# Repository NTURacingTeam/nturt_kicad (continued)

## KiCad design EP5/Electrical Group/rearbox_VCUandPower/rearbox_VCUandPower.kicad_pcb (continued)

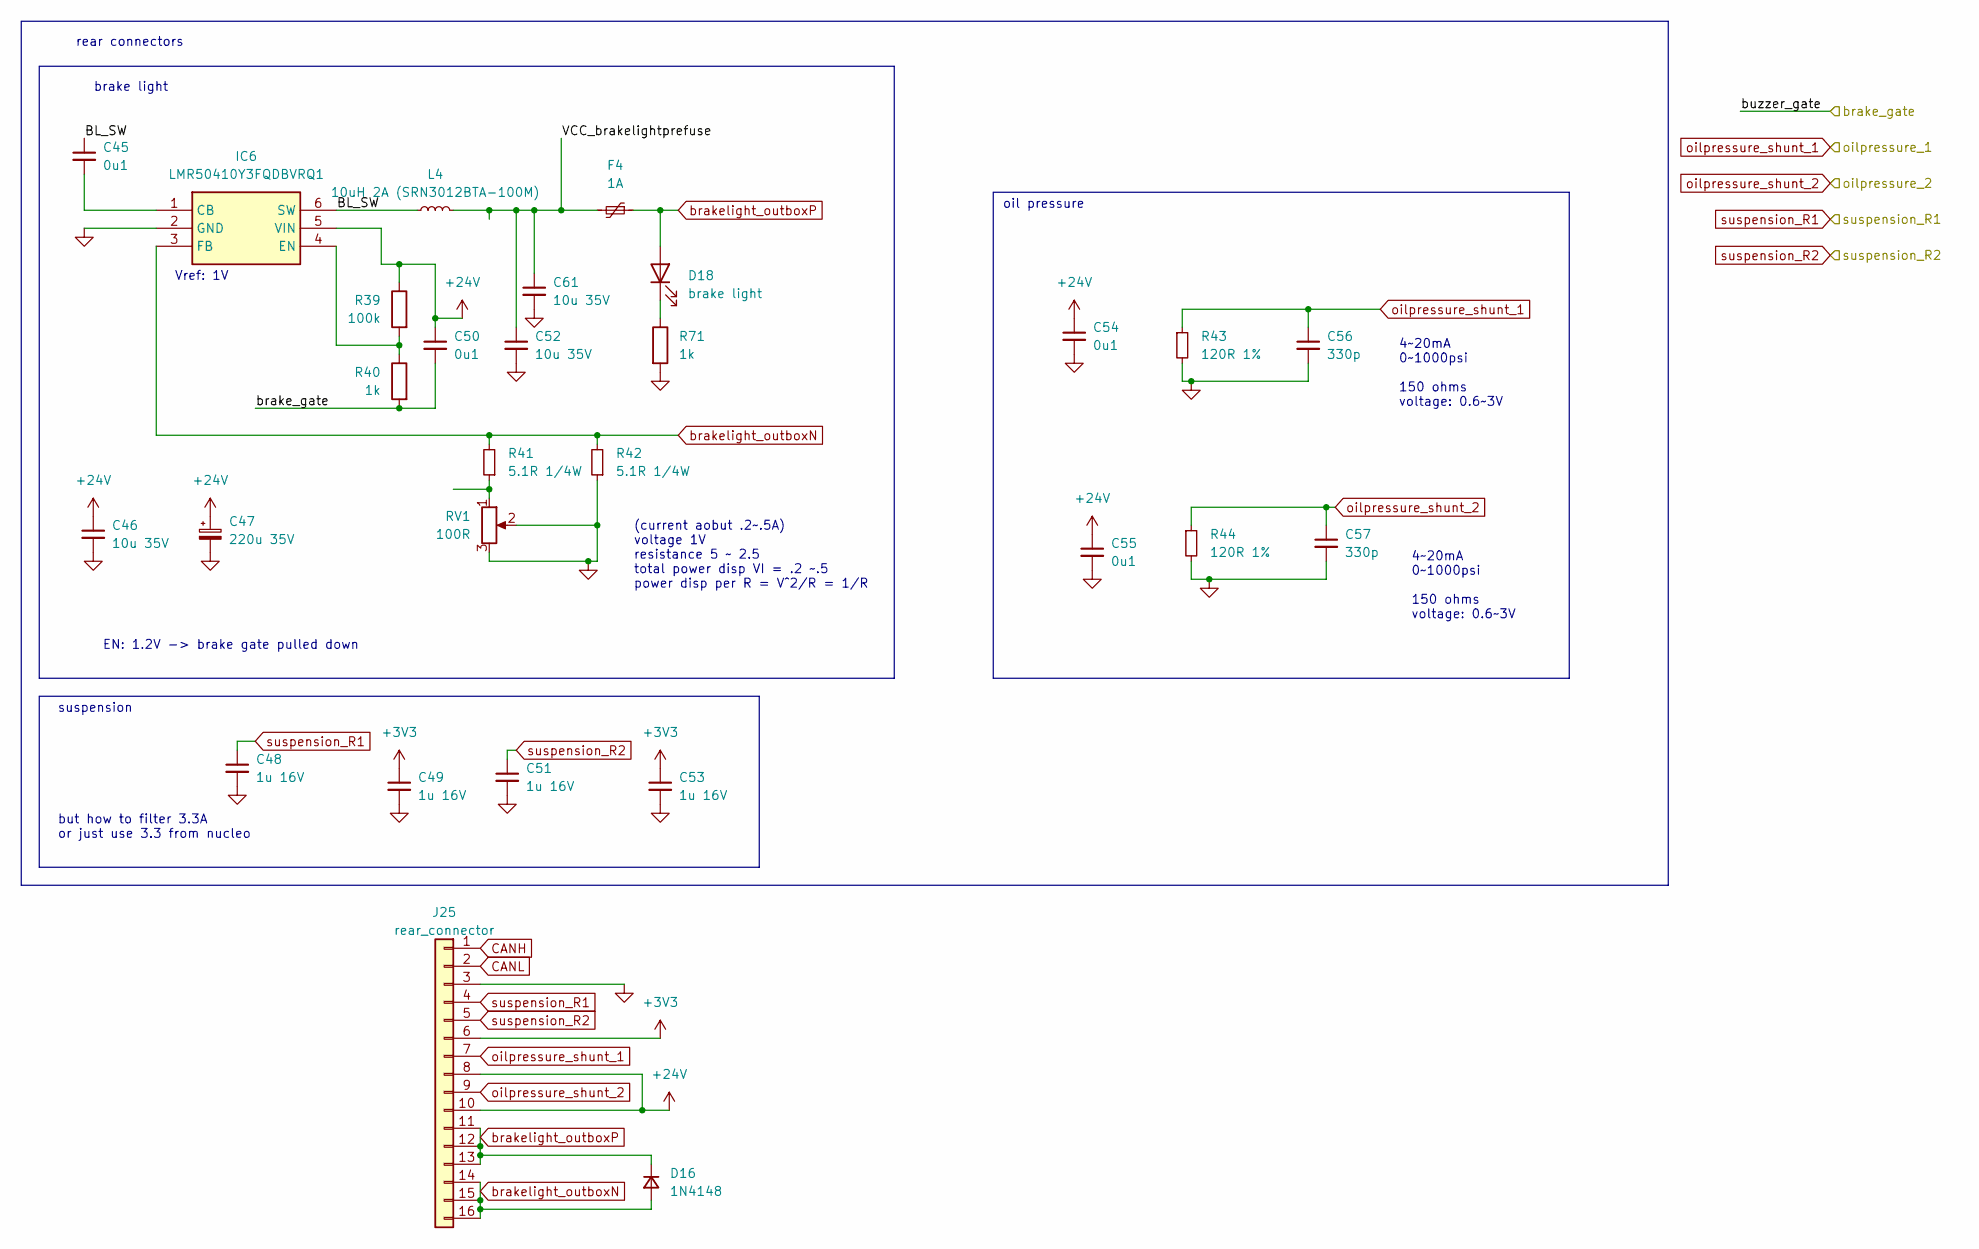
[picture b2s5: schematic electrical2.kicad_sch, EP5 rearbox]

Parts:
C45, C50, C54, C55: 0u1; C_0603_1608Metric
C46, C52, C61: 10u 35V; C_1206_3216Metric
C47: 220u 35V; CP_Radial_D8.0mm_P3.80mm
C48, C49, C51, C53: 1u 16V; C_0603_1608Metric
C56, C57: 330p; C_0603_1608Metric
D16: 1N4148; D_MiniMELF
D18: brake light; LED_0603_1608Metric
F4: 1A; Fuse_1206_3216Metric
IC6: LMR50410Y3FQDBVRQ1; SOT95P280X145-6N; Mouser Part Number 595-R50410Y3FQDBVRQ1
J25: rear_connector; IDC-Header_2x08_P2.54mm_Vertical
L4: 10uH 2A (SRN3012BTA-100M); SRN3012BTA100M
R39: 100k; R_0603_1608Metric
R40, R71: 1k; R_0603_1608Metric
R41, R42: 5.1R 1/4W; R_Axial_DIN0207_L6.3mm_D2.5mm_P7.62mm_Horizontal
R43, R44: 120R 1%; R_0805_2012Metric
RV1: 100R; Potentiometer_Vishay_T73YP_Vertical

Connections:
+3V3: C49.1, C53.1, J25.6; also elsewhere on the board
+24V: C46.1, C47.1, C50.1, C54.1, C55.1, IC6.5 (VIN), J25.8, J25.10, R39.1; also elsewhere on the board
/brake_gate: C50.2, R40.2; also elsewhere on the board
/electrical2/BL_SW: C45.1, IC6.6 (SW), L4.1
/electrical2/VCC_brakelightprefuse: C52.1, C61.1, F4.2, L4.2
CANH: J25.1; also elsewhere on the board
CANL: J25.2; also elsewhere on the board
GND: C46.2, C47.2, C48.2, C49.2, C51.2, C52.2, C53.2, C54.2, C55.2, C56.2, C57.2, C61.2, IC6.2 (GND), J25.3, R42.1, R43.2, R44.2, R71.2, RV1.2, RV1.3; also elsewhere on the board
unnamed: D18.1 (K), R71.1
unnamed: C45.2, IC6.1 (CB)
unnamed: IC6.4 (EN), R39.2, R40.1
unnamed: R41.1, RV1.1
brakelight_outboxN: D16.2 (A), IC6.3 (FB), J25.14, J25.15, J25.16, R41.2, R42.2
brakelight_outboxP: D16.1 (K), D18.2 (A), F4.1, J25.11, J25.12, J25.13
oilpressure_shunt_1: C56.1, J25.7, R43.1; also elsewhere on the board
oilpressure_shunt_2: C57.1, J25.9, R44.1; also elsewhere on the board
suspension_R1: C48.1, J25.4; also elsewhere on the board
suspension_R2: C51.1, J25.5; also elsewhere on the board

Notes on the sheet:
brake light
4~20mA 0~1000psi 150 ohms voltage: 0.6~3V
suspension
(current aobut .2~.5A) voltage 1V resistance 5 ~ 2.5 total power disp VI = .2 ~.5 power disp per R = V^2/R = 1/R
Vref: 1V
oil pressure
EN: 1.2V -> brake gate pulled down
rear connectors
but how to filter 3.3A or just use 3.3 from nucleo

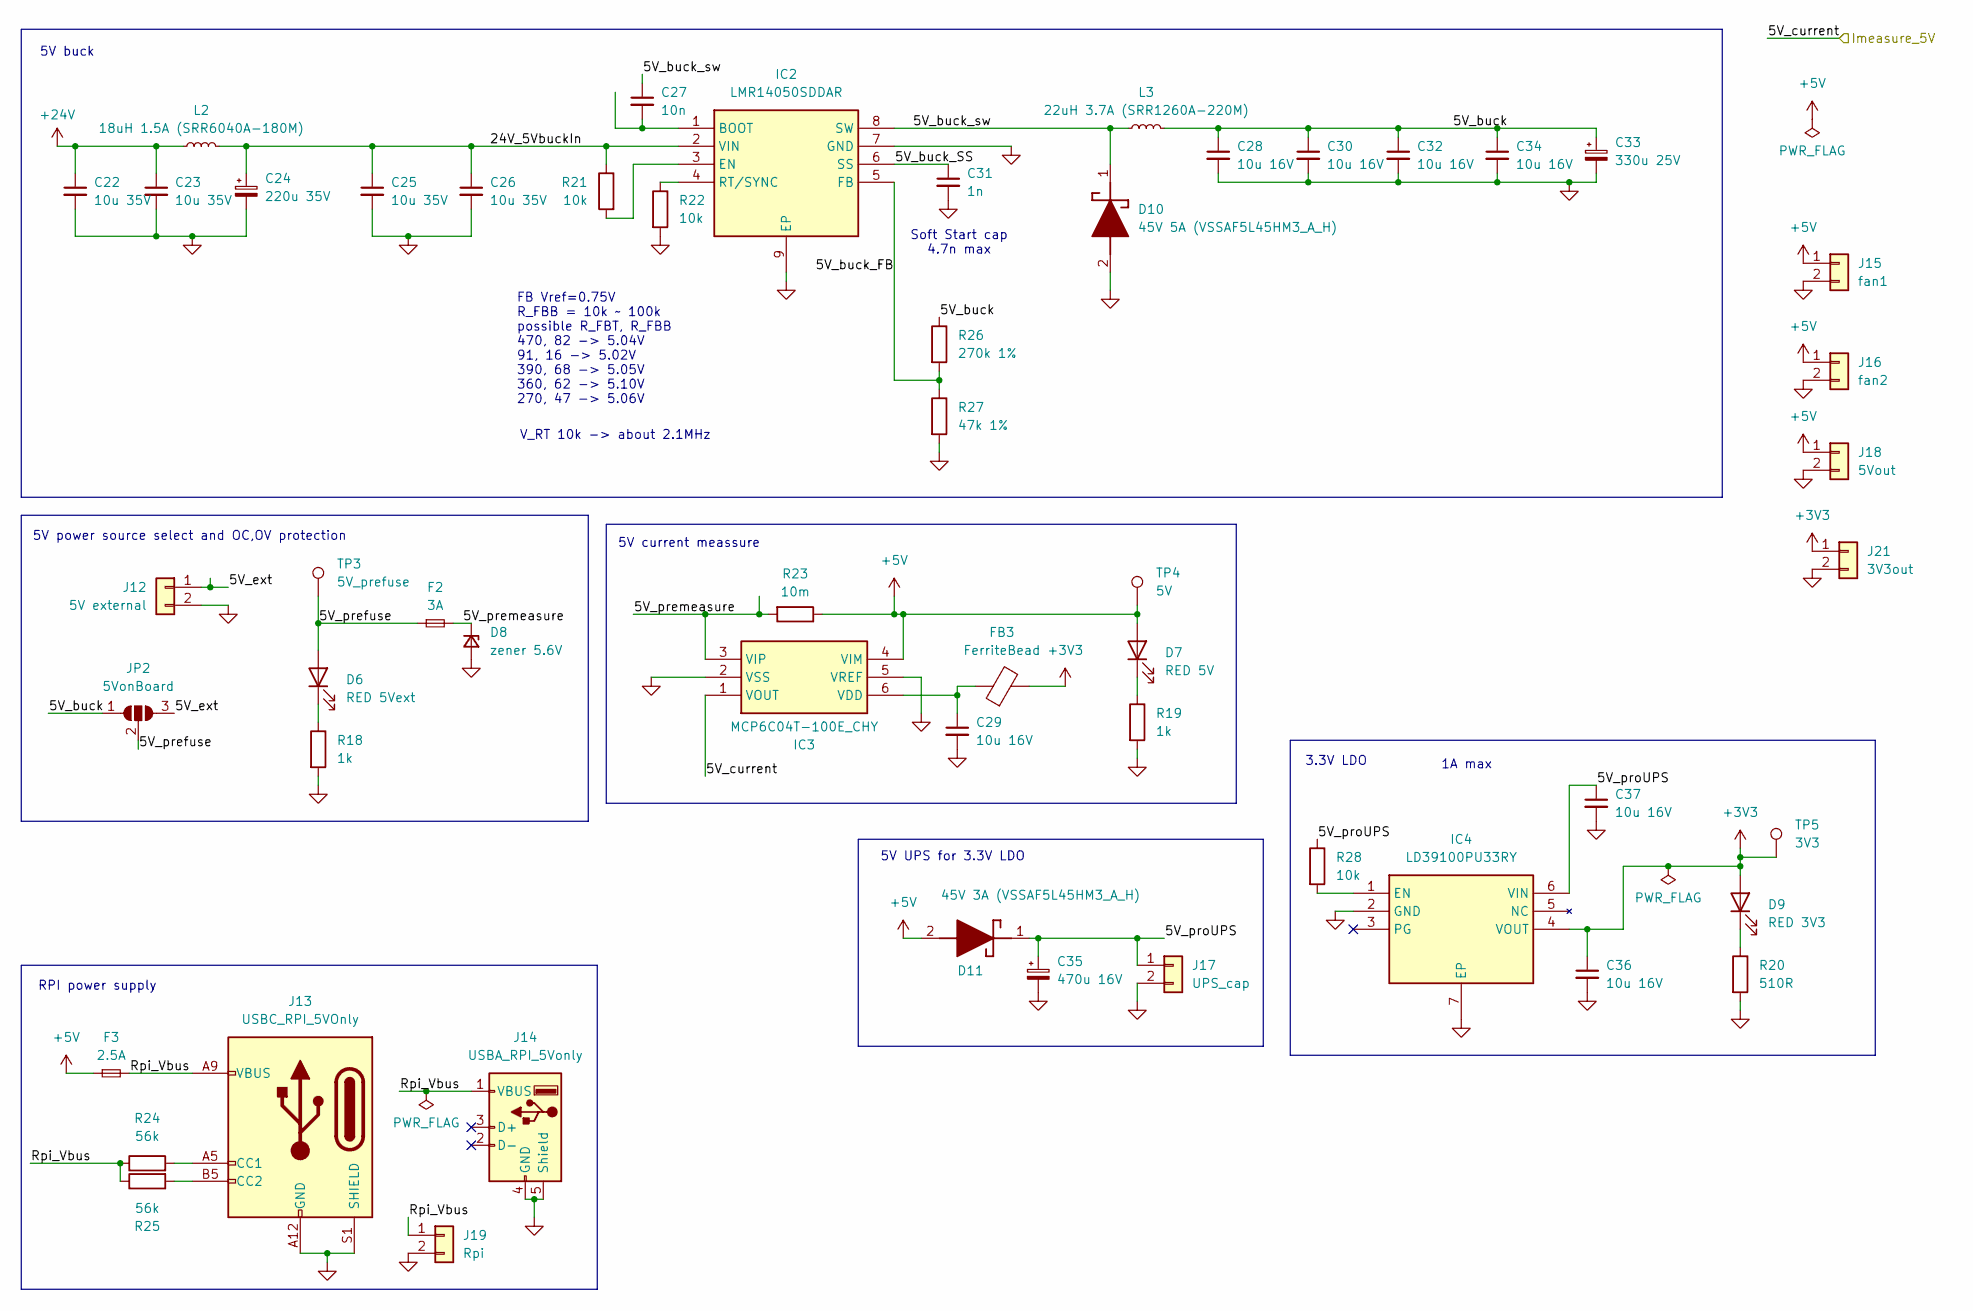
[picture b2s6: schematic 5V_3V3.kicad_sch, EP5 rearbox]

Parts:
C22, C23, C25, C26: 10u 35V; C_1206_3216Metric
C24: 220u 35V; CP_Radial_D8.0mm_P3.80mm
C27: 10n; C_0603_1608Metric
C28, C29, C30, C32, C34, C36, C37: 10u 16V; C_0805_2012Metric
C31: 1n; C_0603_1608Metric
C33: 330u 25V; CP_Radial_D8.0mm_P3.80mm
C35: 470u 16V; CP_Radial_D8.0mm_P3.80mm
D6: RED 5Vext; LED_0603_1608Metric
D7: RED 5V; LED_0603_1608Metric
D8: zener 5.6V; D_MiniMELF
D9: RED 3V3; LED_0603_1608Metric
D10: 45V 5A (VSSAF5L45HM3_A_H); SODFL5226X100N; Mouser Part Number 78-VSSAF5L45HM3_A/H
D11: 45V 3A (VSSAF5L45HM3_A_H); SODFL5226X100N; Mouser Part Number 78-VSSAF5L45HM3_A/H
F2: 3A; Fuse_2512_6332Metric_Pad1.52x3.35mm_HandSolder
F3: 2.5A; Fuse_2512_6332Metric_Pad1.52x3.35mm_HandSolder
FB3: FerriteBead; L_0805_2012Metric
IC2: LMR14050SDDAR; SOIC127P600X170-9N; Mouser Part Number 595-LMR14050SDDAR
IC3: MCP6C04T-100E_CHY; SOT95P280X145-6N; Mouser Part Number 579-MCP6C04T100ECHY
IC4: LD39100PU33RY; SON95P300X300X90-7N-D; Mouser Part Number 511-LD39100PU33RY
J12: 5V external; JST_XH_B2B-XH-A_1x02_P2.50mm_Vertical
J13: USBC_RPI_5VOnly; USB_C_Receptacle_GCT_USB4135-GF-A_6P_TopMnt_Horizontal
J14: USBA_RPI_5Vonly; USB_A_Molex_67643_Horizontal
J15: fan1; JST_XH_B2B-XH-A_1x02_P2.50mm_Vertical
J16: fan2; JST_XH_B2B-XH-A_1x02_P2.50mm_Vertical
J17: UPS_cap; JST_XH_B2B-XH-A_1x02_P2.50mm_Vertical
J18: 5Vout; JST_XH_B2B-XH-A_1x02_P2.50mm_Vertical
J19: Rpi; JST_XH_B2B-XH-A_1x02_P2.50mm_Vertical
J21: 3V3out; JST_XH_B2B-XH-A_1x02_P2.50mm_Vertical
JP2: 5VonBoard; SolderJumper-3_P1.3mm_Open_Pad1.0x1.5mm
L2: 18uH 1.5A (SRR6040A-180M); SRR6040A180M
L3: 22uH 3.7A (SRR1260A-220M); SRR1260A220M
R18, R19: 1k; R_0603_1608Metric
R20: 510R; R_0603_1608Metric
R21, R22, R28: 10k; R_0603_1608Metric
R23: 10m; R_1206_3216Metric
R24, R25: 56k; R_0603_1608Metric
R26: 270k 1%; R_0603_1608Metric
R27: 47k 1%; R_0603_1608Metric
TP3: 5V_prefuse; TestPoint_Pad_D1.0mm
TP4: 5V; TestPoint_Pad_D1.0mm
TP5: 3V3; TestPoint_Pad_D1.0mm

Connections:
+3V3: C36.1, D9.2 (A), FB3.2, IC4.4 (VOUT), J21.1, TP5.1; also elsewhere on the board
+5V: D7.2 (A), D11.2 (A), F3.1, IC3.4 (VIM), J15.1, J16.1, J18.1, R23.1, TP4.1; also elsewhere on the board
+24V: C22.1, C23.1, L2.1; also elsewhere on the board
/5V_3V3/5V_buck: C28.1, C30.1, C32.1, C33.1, C34.1, JP2.1 (A), L3.2, R26.1
/5V_3V3/5V_buck_FB: IC2.5 (FB), R26.2, R27.1
/5V_3V3/5V_buck_SS: C31.1, IC2.6 (SS)
/5V_3V3/5V_buck_sw: C27.1, D10.1 (K), IC2.8 (SW), L3.1
/5V_3V3/5V_ext: J12.1, JP2.3 (B)
/5V_3V3/5V_prefuse: D6.2 (A), F2.1, JP2.2 (C), TP3.1
/5V_3V3/5V_premeasure: D8.1 (K), F2.2, IC3.3 (VIP), R23.2
/5V_3V3/5V_proUPS: C35.1, C37.1, D11.1 (K), IC4.6 (VIN), J17.1, R28.1
/5V_3V3/24V_5VbuckIn: C24.1, C25.1, C26.1, IC2.2 (VIN), L2.2, R21.1
/5V_3V3/Rpi_Vbus: F3.2, J13.A9 (VBUS), J13.B9 (VBUS), J14.1 (VBUS), J19.1, R24.1, R25.1
/I_measure_5v: IC3.1 (VOUT); also elsewhere on the board
GND: C22.2, C23.2, C24.2, C25.2, C26.2, C28.2, C29.2, C30.2, C31.2, C32.2, C33.2, C34.2, C35.2, C36.2, C37.2, D8.2 (A), D10.2 (A), IC2.7 (GND), IC2.9 (EP), IC3.2 (VSS), IC3.5 (VREF), IC4.2 (GND), IC4.7 (EP), J12.2, J13.A12 (GND), J13.B12 (GND), J13.S1 (SHIELD), J14.4 (GND), J14.5 (Shield), J15.2, J16.2, J17.2, J18.2, J19.2, J21.2, R18.2, R19.2, R20.2, R22.2, R27.2; also elsewhere on the board
unnamed: D6.1 (K), R18.1
unnamed: D7.1 (K), R19.1
unnamed: D9.1 (K), R20.1
unnamed: C27.2, IC2.1 (BOOT)
unnamed: IC2.3 (EN), R21.2
unnamed: IC2.4 (RT/SYNC), R22.1
unnamed: C29.1, FB3.1, IC3.6 (VDD)
unnamed: IC4.1 (EN), R28.2
unnamed: J13.A5 (CC1), R24.2
unnamed: J13.B5 (CC2), R25.2

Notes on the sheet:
Soft Start cap 4.7n max
5V UPS for 3.3V LDO
5V power source select and OC,OV protection
RPI power supply
3.3V LDO
V_RT 10k -> about 2.1MHz
5V buck
5V current meassure
FB Vref=0.75V R_FBB = 10k ~ 100k possible R_FBT, R_FBB 470, 82 -> 5.04V 91, 16 -> 5.02V 390, 68 -> 5.05V 360, 62 -> 5.10V 270, 47 -> 5.06V
1A max

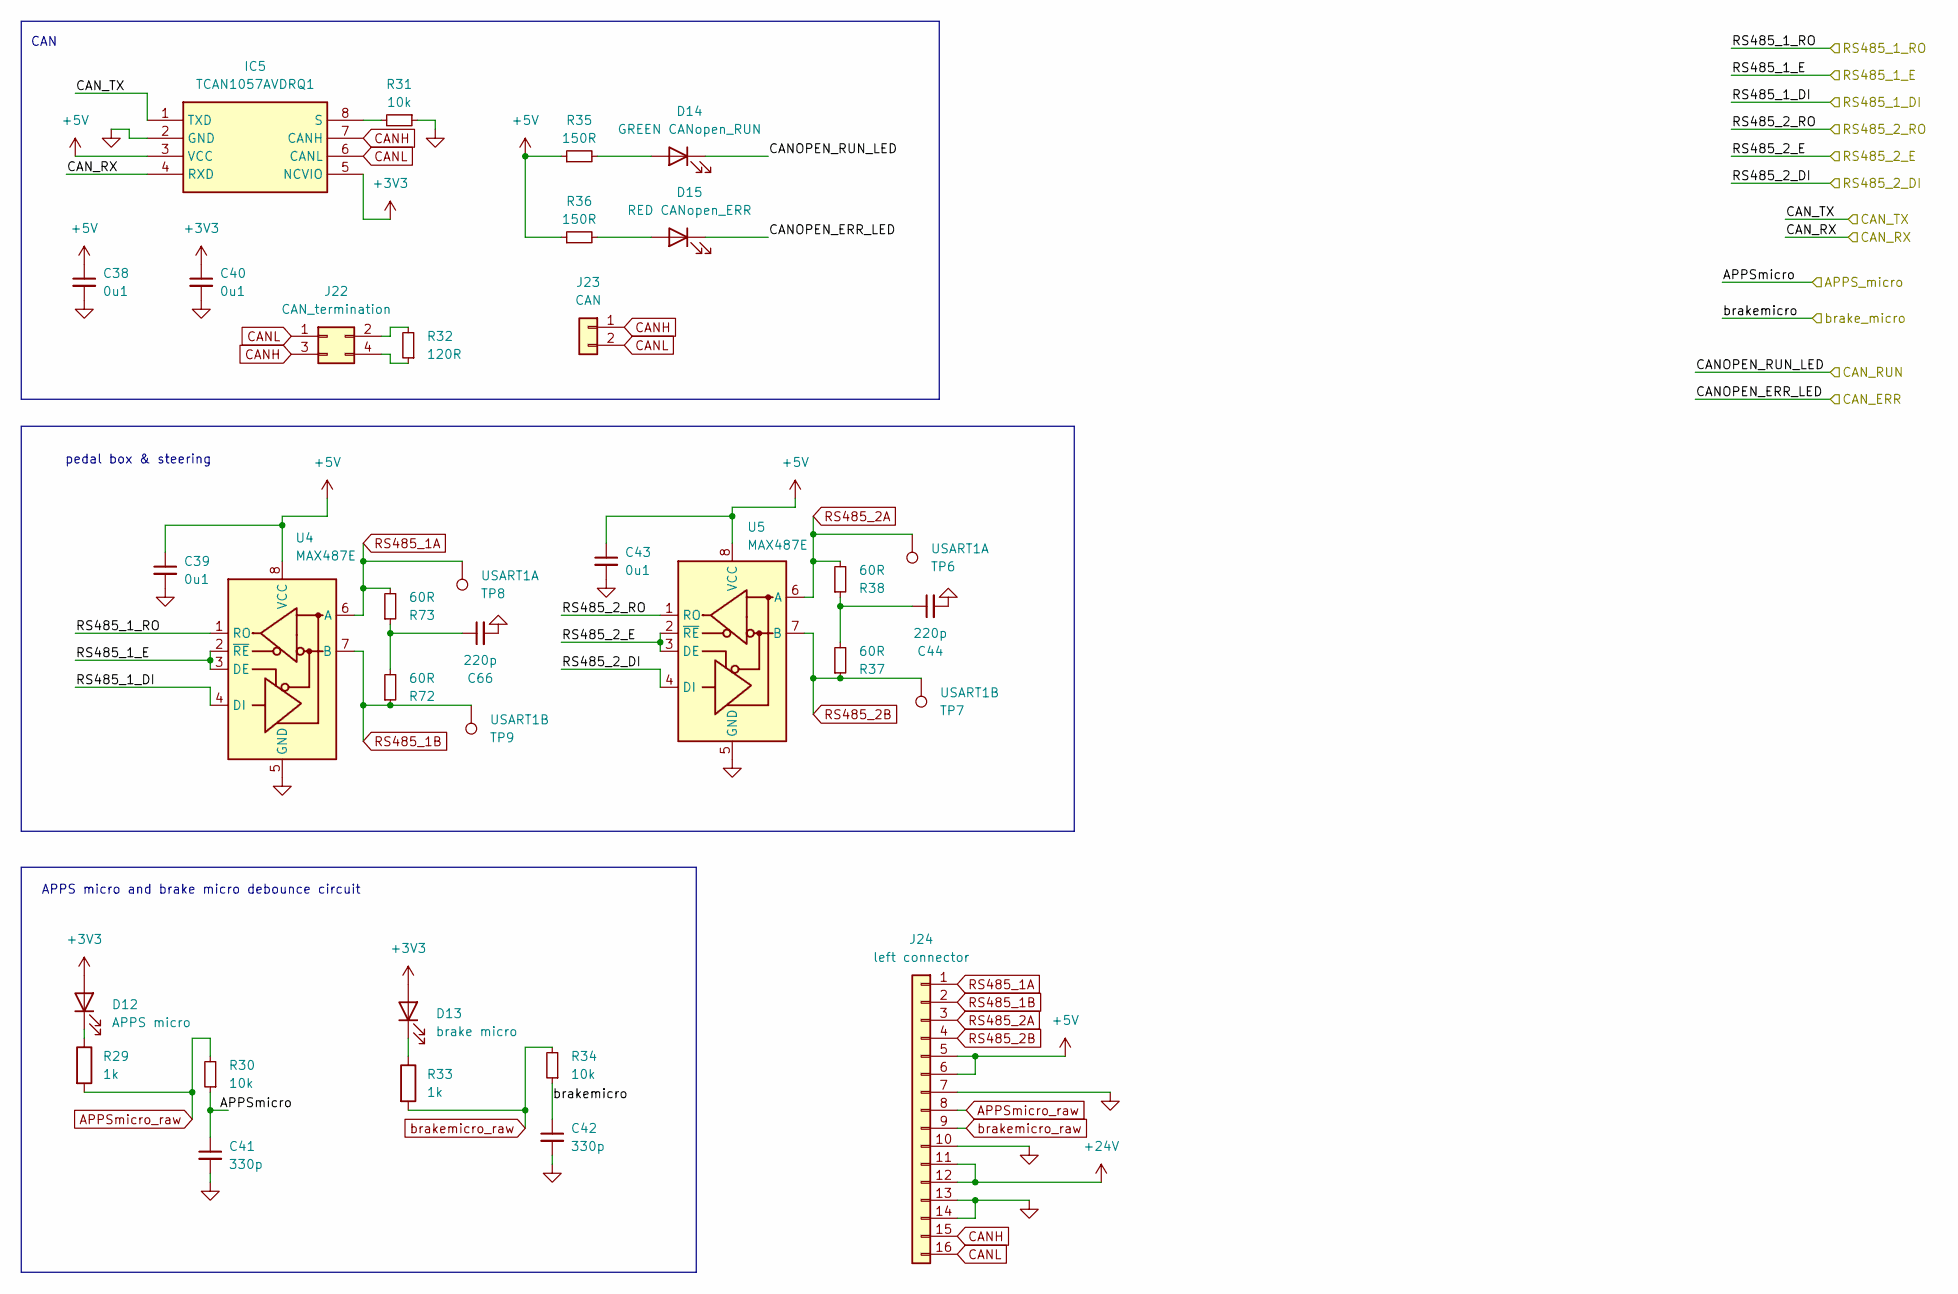
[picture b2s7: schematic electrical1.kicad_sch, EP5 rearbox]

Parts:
C38, C39, C40, C43: 0u1; C_0603_1608Metric
C41, C42: 330p; C_0603_1608Metric
C44, C66: 220p; C_0603_1608Metric
D12: APPS micro; LED_0603_1608Metric
D13: brake micro; LED_0603_1608Metric
D14: GREEN CANopen_RUN; LED_0603_1608Metric
D15: RED CANopen_ERR; LED_0603_1608Metric
IC5: TCAN1057AVDRQ1; SOIC127P600X175-8N; Mouser Part Number 595-TCAN1057AVDRQ1
J22: CAN_termination; PinHeader_2x02_P2.54mm_Vertical
J23: CAN; JST_XH_B2B-XH-A_1x02_P2.50mm_Vertical
J24: left connector; IDC-Header_2x08_P2.54mm_Vertical
R29, R33: 1k; R_0603_1608Metric
R30, R31, R34: 10k; R_0603_1608Metric
R32: 120R; R_0603_1608Metric
R35, R36: 150R; R_0603_1608Metric
R37, R38, R72, R73: 60R; R_0603_1608Metric
TP6, TP8: USART1A; TestPoint_Pad_D1.0mm
TP7, TP9: USART1B; TestPoint_Pad_D1.0mm
U4, U5: MAX487E; SOIC-8_3.9x4.9mm_P1.27mm

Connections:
+3V3: C40.1, D12.2 (A), D13.2 (A), IC5.5 (NCVIO); also elsewhere on the board
+5V: C38.1, C39.1, C43.1, IC5.3 (VCC), J24.5, J24.6, R35.1, R36.1, U4.8 (VCC), U5.8 (VCC); also elsewhere on the board
+24V: J24.11, J24.12; also elsewhere on the board
/APPSmicro: C41.1, R30.1; also elsewhere on the board
/CAN_ERR: D15.1 (K); also elsewhere on the board
/CAN_RUN: D14.1 (K); also elsewhere on the board
/FDCAN1_RX: IC5.4 (RXD); also elsewhere on the board
/FDCAN1_TX: IC5.1 (TXD); also elsewhere on the board
/UART4_DE: U4.2 (~RE), U4.3 (DE); also elsewhere on the board
/UART4_RX: U4.1 (RO); also elsewhere on the board
/UART4_TX: U4.4 (DI); also elsewhere on the board
/UART5_DE: U5.2 (~RE), U5.3 (DE); also elsewhere on the board
/UART5_RX: U5.1 (RO); also elsewhere on the board
/UART5_TX: U5.4 (DI); also elsewhere on the board
/brakemicro: C42.1, R34.1; also elsewhere on the board
APPSmicro_raw: J24.8, R29.2, R30.2
CANH: IC5.7 (CANH), J22.3, J23.1, J24.15; also elsewhere on the board
CANL: IC5.6 (CANL), J22.1, J23.2, J24.16; also elsewhere on the board
GND: C38.2, C39.2, C40.2, C41.2, C42.2, C43.2, C44.2, C66.2, IC5.2 (GND), J24.7, J24.10, J24.13, J24.14, R31.1, U4.5 (GND), U5.5 (GND); also elsewhere on the board
unnamed: C44.1, R37.2, R38.1
unnamed: C66.1, R72.2, R73.1
unnamed: D12.1 (K), R29.1
unnamed: D13.1 (K), R33.1
unnamed: D14.2 (A), R35.2
unnamed: D15.2 (A), R36.2
unnamed: IC5.8 (S), R31.2
unnamed: J22.2, R32.2
unnamed: J22.4, R32.1
RS485_1A: J24.1, R73.2, TP8.1, U4.6 (A)
RS485_1B: J24.2, R72.1, TP9.1, U4.7 (B)
RS485_2A: J24.3, R38.2, TP6.1, U5.6 (A)
RS485_2B: J24.4, R37.1, TP7.1, U5.7 (B)
brakemicro_raw: J24.9, R33.2, R34.2

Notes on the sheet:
CAN
APPS micro and brake micro debounce circuit
pedal box & steering

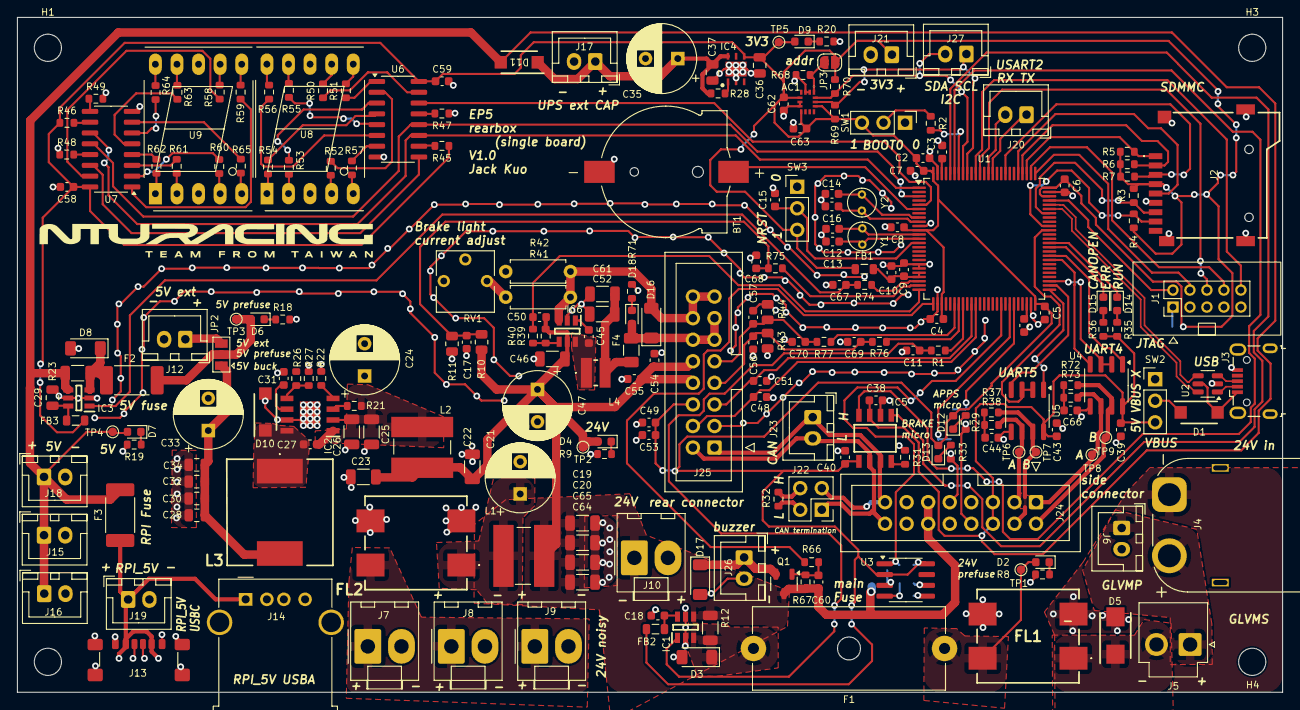
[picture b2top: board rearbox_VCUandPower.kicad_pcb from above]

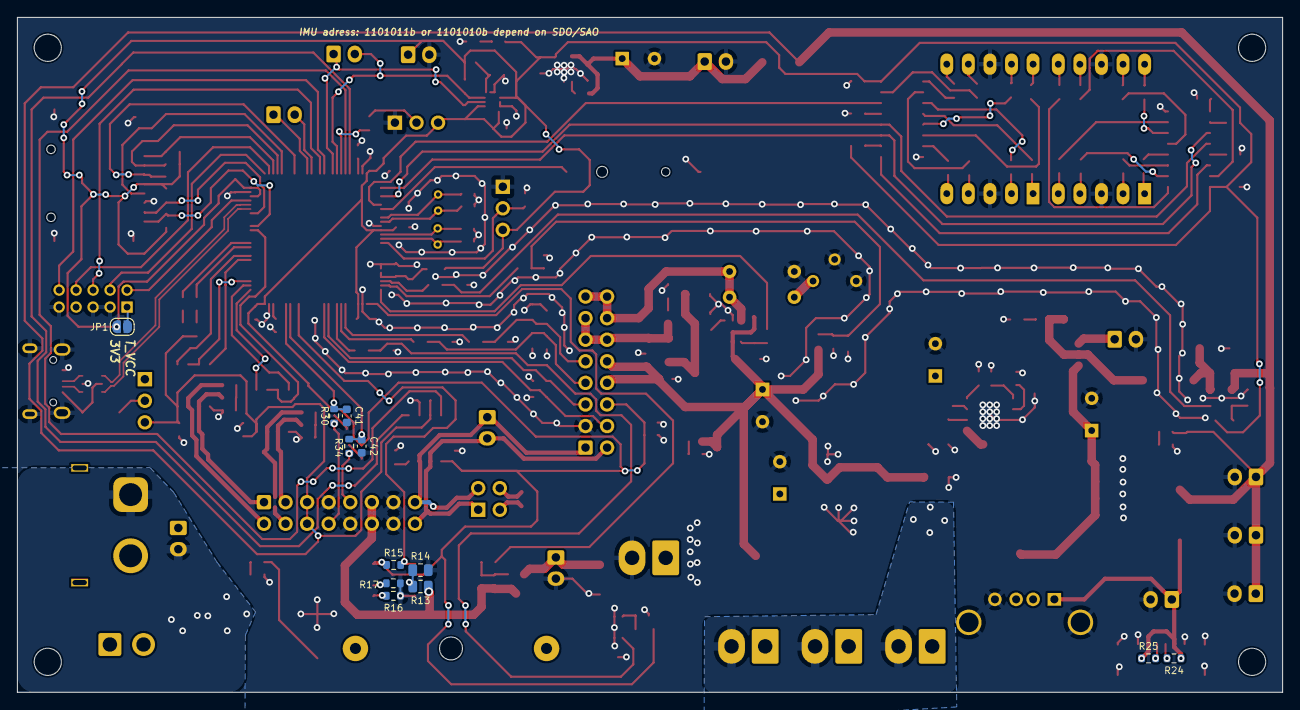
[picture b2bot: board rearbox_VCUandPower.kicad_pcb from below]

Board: 2 copper layers, 148.9 x 79.5 mm, 244 parts (12 on the bottom side), 167 nets.

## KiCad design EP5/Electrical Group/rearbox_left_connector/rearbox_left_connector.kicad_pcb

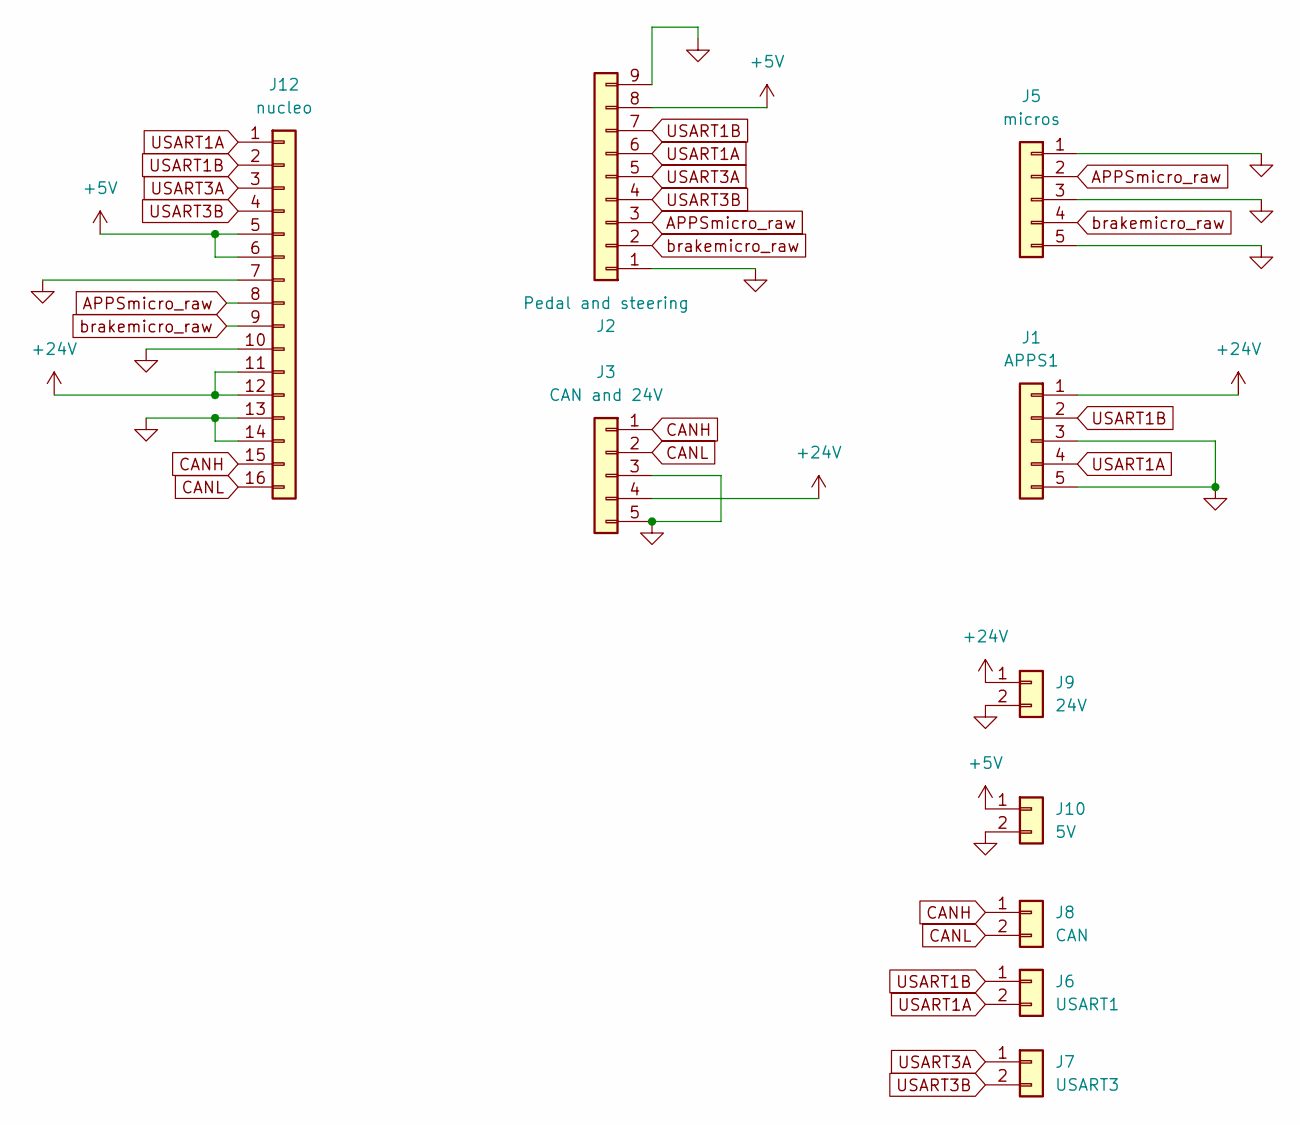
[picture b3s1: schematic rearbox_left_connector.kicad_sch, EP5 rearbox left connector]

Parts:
J1: APPS1; WP-04F3-26-11
J2: Pedal and steering; WP-08M3-14-11
J3: CAN and 24V; WP-04F3-26-11
J5: micros; WP-04F3-26-11
J6: USART1; JST_XH_B2B-XH-A_1x02_P2.50mm_Vertical
J7: USART3; JST_XH_B2B-XH-A_1x02_P2.50mm_Vertical
J8: CAN; JST_XH_B2B-XH-A_1x02_P2.50mm_Vertical
J9: 24V; JST_XH_B2B-XH-A_1x02_P2.50mm_Vertical
J10: 5V; JST_XH_B2B-XH-A_1x02_P2.50mm_Vertical
J12: nucleo; IDC-Header_2x08_P2.54mm_Vertical

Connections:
+5V: J2.8, J10.1; also elsewhere on the board
+24V: J1.1, J3.4, J9.1; also elsewhere on the board
APPSmicro_raw: J2.3, J5.2; also elsewhere on the board
CANH: J3.1, J8.1; also elsewhere on the board
CANL: J3.2, J8.2; also elsewhere on the board
GND: J1.3, J1.5, J2.1, J2.9, J3.3, J3.5, J5.1, J5.3, J5.5, J9.2, J10.2; also elsewhere on the board
USART1A: J1.4, J2.6, J6.2; also elsewhere on the board
USART1B: J1.2, J2.7, J6.1; also elsewhere on the board
USART3A: J2.5, J7.1; also elsewhere on the board
USART3B: J2.4, J7.2; also elsewhere on the board
brakemicro_raw: J2.2, J5.4; also elsewhere on the board

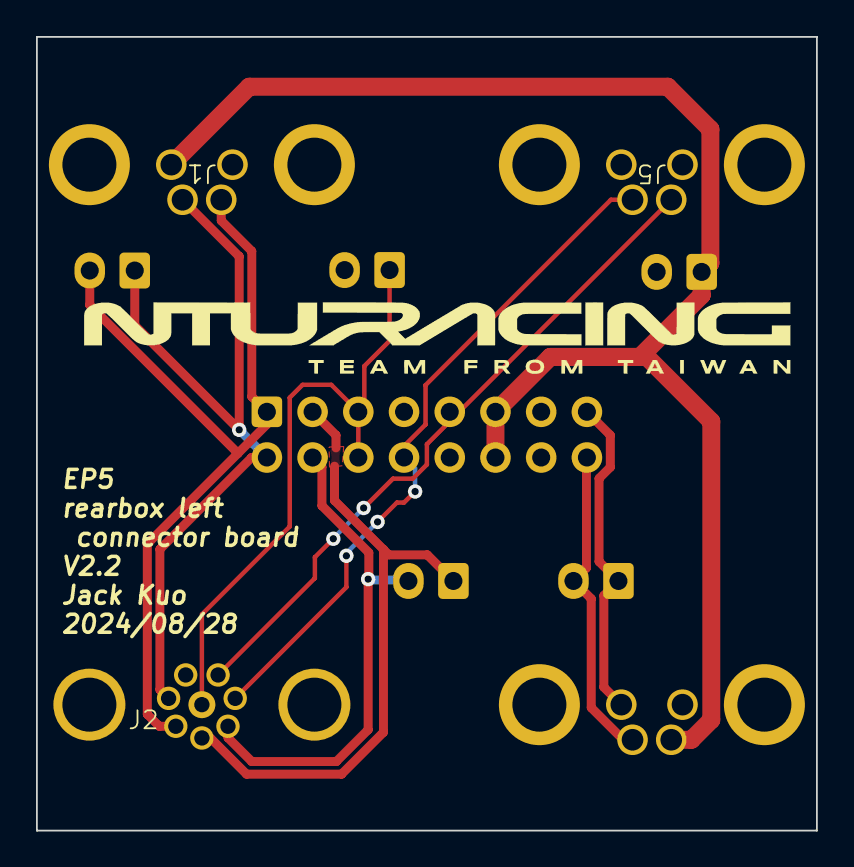
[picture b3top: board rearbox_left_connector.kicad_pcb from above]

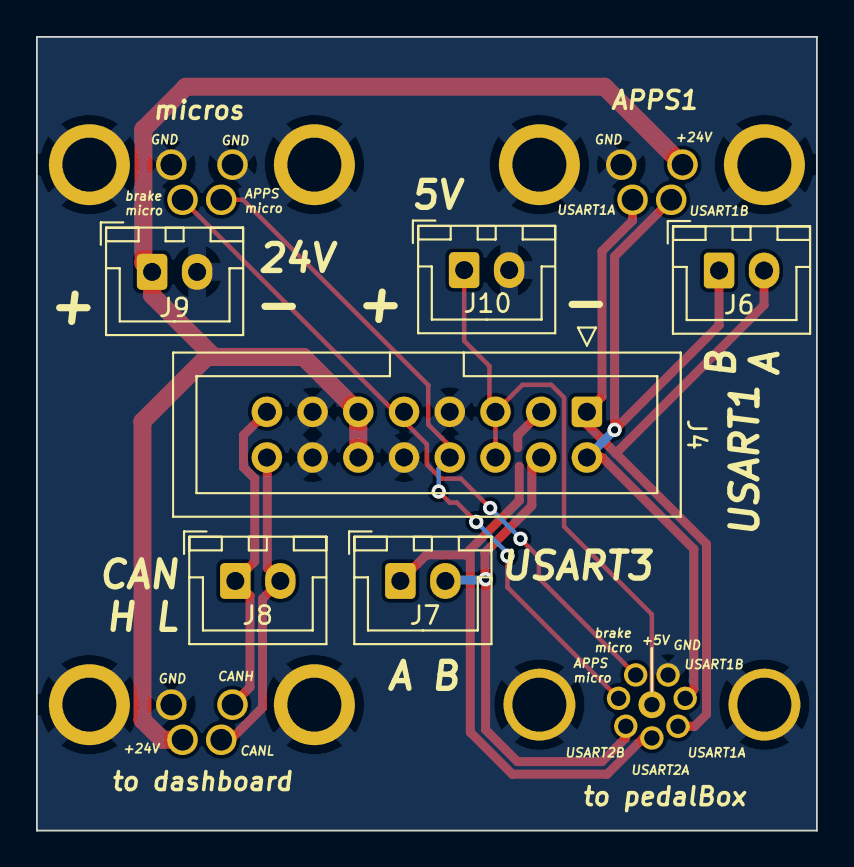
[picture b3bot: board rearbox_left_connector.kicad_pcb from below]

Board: 2 copper layers, 43.3 x 44.1 mm, 10 parts (6 on the bottom side), 11 nets.

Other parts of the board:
J4: nucleo; IDC-Header_2x08_P2.54mm_Vertical

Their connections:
+5V: J4.5, J4.6; also elsewhere on the board
+24V: J4.11, J4.12; also elsewhere on the board
APPSmicro_raw: J4.8; also elsewhere on the board
CANH: J4.15; also elsewhere on the board
CANL: J4.16; also elsewhere on the board
GND: J4.7, J4.10, J4.13, J4.14; also elsewhere on the board
USART1A: J4.1; also elsewhere on the board
USART1B: J4.2; also elsewhere on the board
USART3A: J4.3; also elsewhere on the board
USART3B: J4.4; also elsewhere on the board
brakemicro_raw: J4.9; also elsewhere on the board

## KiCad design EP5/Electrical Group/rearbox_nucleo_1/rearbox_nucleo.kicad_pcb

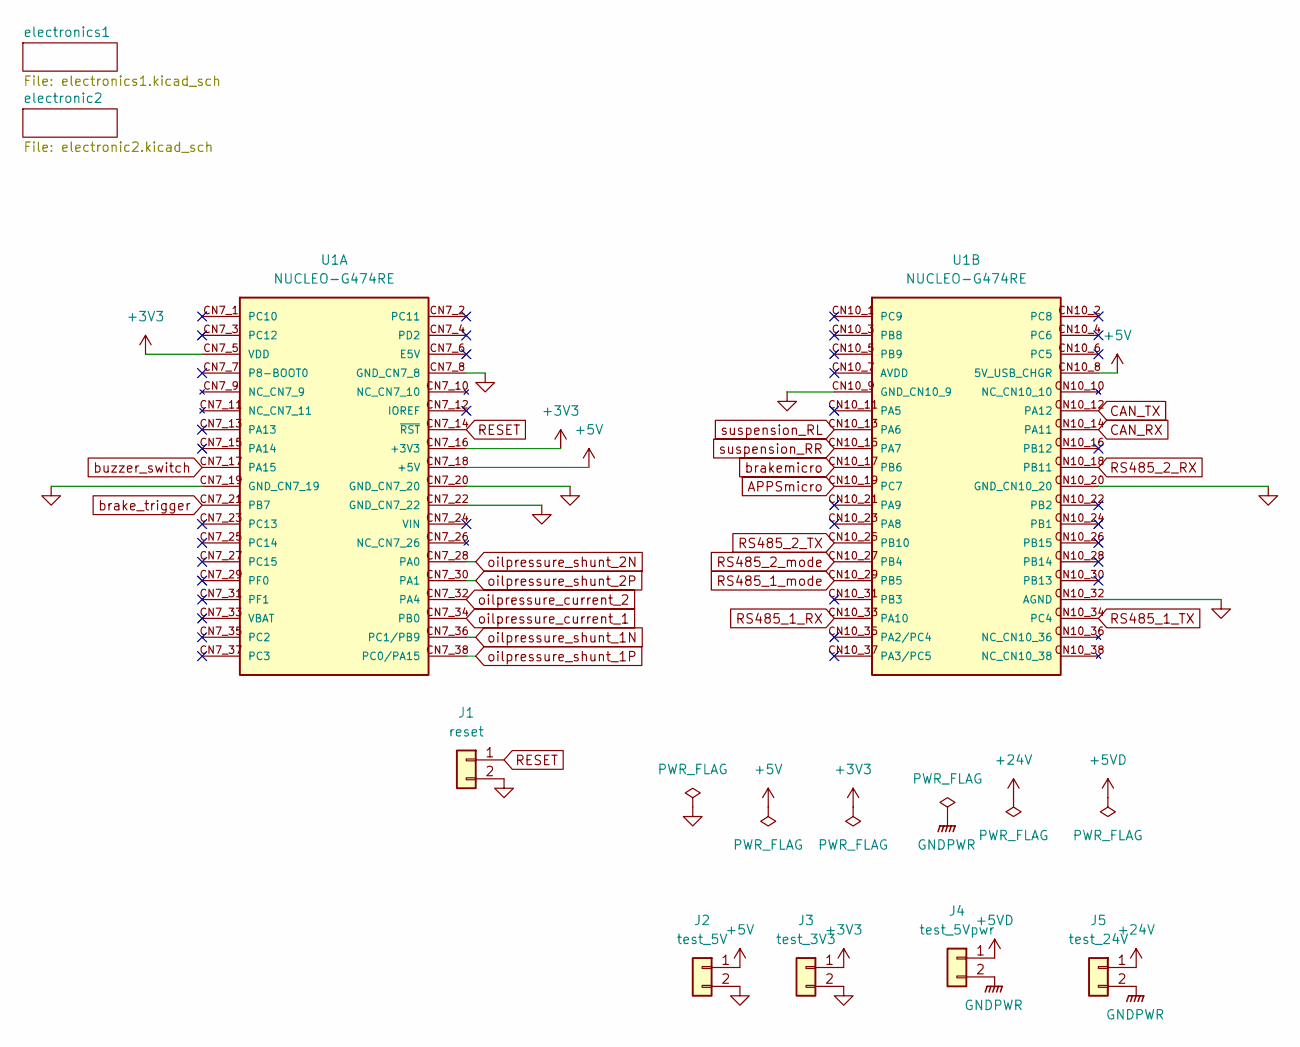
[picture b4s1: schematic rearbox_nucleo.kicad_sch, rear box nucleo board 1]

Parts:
J1: reset; JST_XH_B2B-XH-A_1x02_P2.50mm_Vertical
J2: test_5V; PinHeader_1x02_P2.54mm_Vertical
J3: test_3V3; PinHeader_1x02_P2.54mm_Vertical
J4: test_5Vpwr; PinHeader_1x02_P2.54mm_Vertical
J5: test_24V; PinHeader_1x02_P2.54mm_Vertical
U1: NUCLEO-G474RE; MODULE_NUCLEO-G474RE; PARTREV 17

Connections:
+3V3: J3.1, U1.CN7_5 (VDD), U1.CN7_16 (+3V3); also elsewhere on the board
+5V: J2.1, U1.CN7_18 (+5V), U1.CN10_8 (5V_USB_CHGR); also elsewhere on the board
+5VD: J4.1; also elsewhere on the board
APPSmicro: U1.CN10_19 (PC7); also elsewhere on the board
CAN_RX: U1.CN10_14 (PA11); also elsewhere on the board
CAN_TX: U1.CN10_12 (PA12); also elsewhere on the board
GND: J1.2, J2.2, J3.2, U1.CN7_8 (GND_CN7_8), U1.CN7_19 (GND_CN7_19), U1.CN7_20 (GND_CN7_20), U1.CN7_22 (GND_CN7_22), U1.CN10_9 (GND_CN10_9), U1.CN10_20 (GND_CN10_20), U1.CN10_32 (AGND); also elsewhere on the board
GNDPWR: J4.2, J5.2; also elsewhere on the board
RESET: J1.1, U1.CN7_14 (~RST)
RS485_1_RX: U1.CN10_33 (PA10); also elsewhere on the board
RS485_1_TX: U1.CN10_34 (PC4); also elsewhere on the board
RS485_1_mode: U1.CN10_29 (PB5); also elsewhere on the board
RS485_2_RX: U1.CN10_18 (PB11); also elsewhere on the board
RS485_2_TX: U1.CN10_25 (PB10); also elsewhere on the board
RS485_2_mode: U1.CN10_27 (PB4); also elsewhere on the board
brake_trigger: U1.CN7_21 (PB7); also elsewhere on the board
brakemicro: U1.CN10_17 (PB6); also elsewhere on the board
buzzer_switch: U1.CN7_17 (PA15); also elsewhere on the board
oilpressure_current_1: U1.CN7_34 (PB0); also elsewhere on the board
oilpressure_current_2: U1.CN7_32 (PA4); also elsewhere on the board
oilpressure_shunt_1N: U1.CN7_36 (PC1/PB9); also elsewhere on the board
oilpressure_shunt_1P: U1.CN7_38 (PC0/PA15); also elsewhere on the board
oilpressure_shunt_2N: U1.CN7_28 (PA0); also elsewhere on the board
oilpressure_shunt_2P: U1.CN7_30 (PA1); also elsewhere on the board
suspension_RL: U1.CN10_13 (PA6); also elsewhere on the board
suspension_RR: U1.CN10_15 (PA7); also elsewhere on the board
